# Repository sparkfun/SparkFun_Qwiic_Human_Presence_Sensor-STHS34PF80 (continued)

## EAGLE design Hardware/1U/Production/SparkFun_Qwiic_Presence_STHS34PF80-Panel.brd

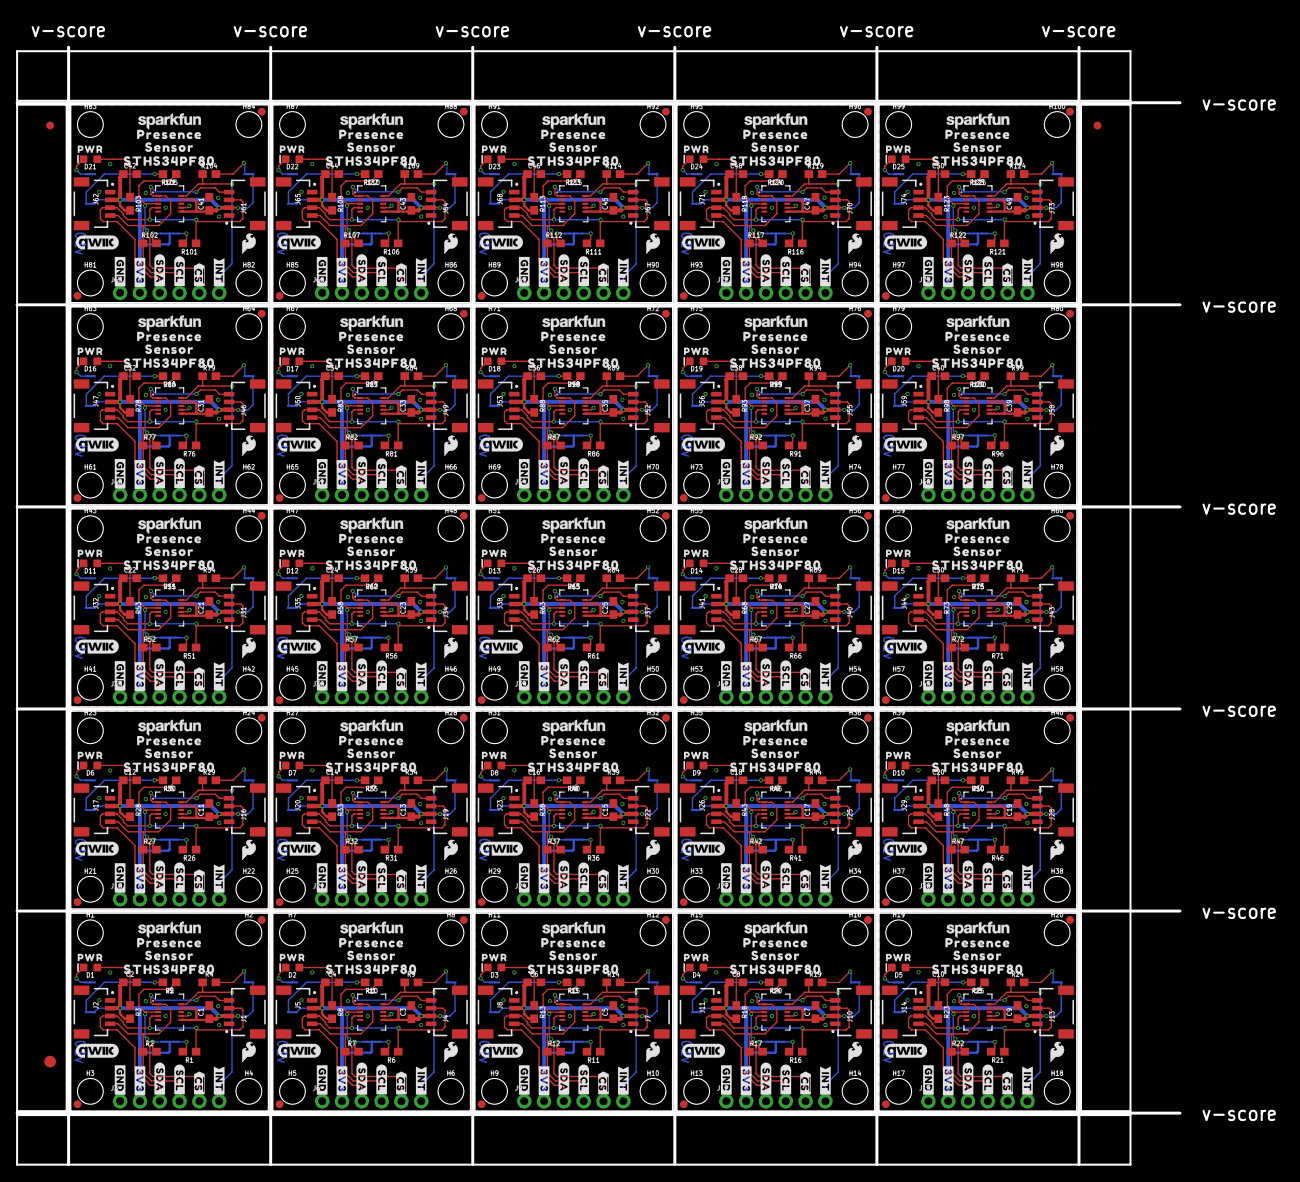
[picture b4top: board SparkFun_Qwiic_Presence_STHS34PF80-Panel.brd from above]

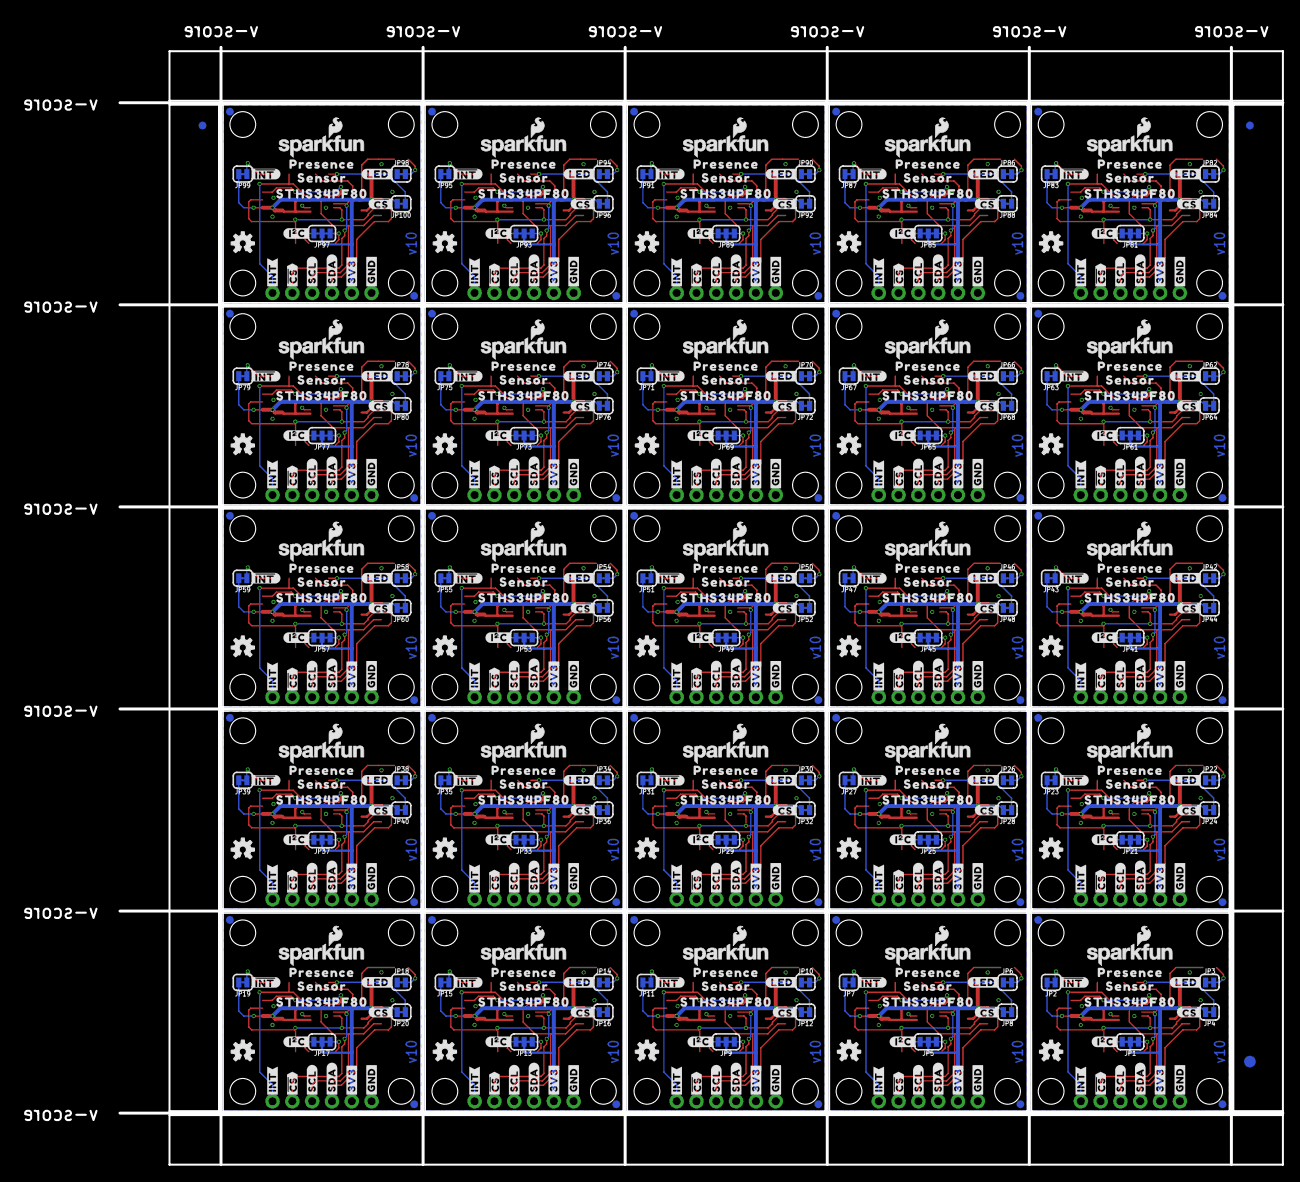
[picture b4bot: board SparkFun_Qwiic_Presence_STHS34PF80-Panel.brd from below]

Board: 2 copper layers, 149.1 x 143.3 mm, 1306 parts (528 on the bottom side), 300 nets.

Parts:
C1, C3, C5, C7, C9, C11, C13, C15, C17, C19, C21, C23, C25, C27, C29, C31, C33, C35, C37, C39, C41, C43, C45, C47, C49: 1.0uF; 0603
C2, C4, C6, C8, C10, C12, C14, C16, C18, C20, C22, C24, C26, C28, C30, C32, C34, C36, C38, C40, C42, C44, C46, C48, C50: 0.1uF; 0603
D1, D2, D3, D4, D5, D6, D7, D8, D9, D10, D11, D12, D13, D14, D15, D16, D17, D18, D19, D20, D21, D22, D23, D24, D25: RED; LED-0603
E$1, E$2, E$3, E$4: FIDUCIAL-1X2
E$5, E$6: FIDUCIAL-1.5X3
FD1, FD2, FD3, FD4, FD5, FD6, FD7, FD8, FD9, FD10, FD11, FD12, FD13, FD14, FD15, FD16, FD17, FD18, FD19, FD20, FD21, FD22, FD23, FD24, FD25, FD26, FD27, FD28, FD29, FD30, FD31, FD32, FD33, FD34, FD35, FD36, FD37, FD38, FD39, FD40, FD41, FD42, FD43, FD44, FD45, FD46, FD47, FD48, FD49, FD50, FD51, FD52, FD53, FD54, FD55, FD56, FD57, FD58, FD59, FD60, FD61, FD62, FD63, FD64, FD65, FD66, FD67, FD68, FD69, FD70, FD71, FD72, FD73, FD74, FD75, FD76, FD77, FD78, FD79, FD80, FD81, FD82, FD83, FD84, FD85, FD86, FD87, FD88, FD89, FD90, FD91, FD92, FD93, FD94, FD95, FD96, FD97, FD98, FD99, FD100: FIDUCIAL1X2; FIDUCIAL-1X2
H1, H2, H3, H4, H5, H6, H7, H8, H9, H10, H11, H12, H13, H14, H15, H16, H17, H18, H19, H20, H21, H22, H23, H24, H25, H26, H27, H28, H29, H30, H31, H32, H33, H34, H35, H36, H37, H38, H39, H40, H41, H42, H43, H44, H45, H46, H47, H48, H49, H50, H51, H52, H53, H54, H55, H56, H57, H58, H59, H60, H61, H62, H63, H64, H65, H66, H67, H68, H69, H70, H71, H72, H73, H74, H75, H76, H77, H78, H79, H80, H81, H82, H83, H84, H85, H86, H87, H88, H89, H90, H91, H92, H93, H94, H95, H96, H97, H98, H99, H100: STAND-OFF
J1, J2, J4, J5, J7, J8, J10, J11, J13, J14, J16, J17, J19, J20, J22, J23, J25, J26, J28, J29, J31, J32, J34, J35, J37, J38, J40, J41, J43, J44, J46, J47, J49, J50, J52, J53, J55, J56, J58, J59, J61, J62, J64, J65, J67, J68, J70, J71, J73, J74: Qwiic; JST04_1MM_RA
J3, J6, J9, J12, J15, J18, J21, J24, J27, J30, J33, J36, J39, J42, J45, J48, J51, J54, J57, J60, J63, J66, J69, J72, J75: 1X06_NO_SILK
JP1, JP5, JP9, JP13, JP17, JP21, JP25, JP29, JP33, JP37, JP41, JP45, JP49, JP53, JP57, JP61, JP65, JP69, JP73, JP77, JP81, JP85, JP89, JP93, JP97: JUMPER-SMT_3_2-NC_TRACE_SILK; SMT-JUMPER_3_2-NC_TRACE_SILK
JP2, JP3, JP4, JP6, JP7, JP8, JP10, JP11, JP12, JP14, JP15, JP16, JP18, JP19, JP20, JP22, JP23, JP24, JP26, JP27, JP28, JP30, JP31, JP32, JP34, JP35, JP36, JP38, JP39, JP40, JP42, JP43, JP44, JP46, JP47, JP48, JP50, JP51, JP52, JP54, JP55, JP56, JP58, JP59, JP60, JP62, JP63, JP64, JP66, JP67, JP68, JP70, JP71, JP72, JP74, JP75, JP76, JP78, JP79, JP80, JP82, JP83, JP84, JP86, JP87, JP88, JP90, JP91, JP92, JP94, JP95, JP96, JP98, JP99, JP100: JUMPER-SMT_2_NC_TRACE_SILK; SMT-JUMPER_2_NC_TRACE_SILK
LOGO1, LOGO5, LOGO11, LOGO16, LOGO21, LOGO26, LOGO31, LOGO36, LOGO41, LOGO46, LOGO51, LOGO56, LOGO61, LOGO66, LOGO71, LOGO76, LOGO81, LOGO86, LOGO91, LOGO96, LOGO101, LOGO106, LOGO111, LOGO116, LOGO121: OSHW-LOGOS; OSHW-LOGO-S
LOGO2, LOGO8, LOGO13, LOGO18, LOGO23, LOGO28, LOGO33, LOGO38, LOGO43, LOGO48, LOGO53, LOGO58, LOGO63, LOGO68, LOGO73, LOGO78, LOGO83, LOGO88, LOGO93, LOGO98, LOGO103, LOGO108, LOGO113, LOGO118, LOGO123: SFE_LOGO_NAME_FLAME.1_INCH; SFE_LOGO_NAME_FLAME_.1
LOGO3, LOGO7, LOGO12, LOGO17, LOGO22, LOGO27, LOGO32, LOGO37, LOGO42, LOGO47, LOGO52, LOGO57, LOGO62, LOGO67, LOGO72, LOGO77, LOGO82, LOGO87, LOGO92, LOGO97, LOGO102, LOGO107, LOGO112, LOGO117, LOGO122: QWIIC_LOGO_CONNECTOR; QWIIC_5.5MM
LOGO4, LOGO10, LOGO15, LOGO20, LOGO25, LOGO30, LOGO35, LOGO40, LOGO45, LOGO50, LOGO55, LOGO60, LOGO65, LOGO70, LOGO75, LOGO80, LOGO85, LOGO90, LOGO95, LOGO100, LOGO105, LOGO110, LOGO115, LOGO120, LOGO125: SFE_LOGO_NAME8_MM; SFE_LOGO_NAME_8MM
LOGO6, LOGO9, LOGO14, LOGO19, LOGO24, LOGO29, LOGO34, LOGO39, LOGO44, LOGO49, LOGO54, LOGO59, LOGO64, LOGO69, LOGO74, LOGO79, LOGO84, LOGO89, LOGO94, LOGO99, LOGO104, LOGO109, LOGO114, LOGO119, LOGO124: SFE_LOGO_FLAME.1_INCH; SFE_LOGO_FLAME_.1
R1, R2, R6, R7, R11, R12, R16, R17, R21, R22, R26, R27, R31, R32, R36, R37, R41, R42, R46, R47, R51, R52, R56, R57, R61, R62, R66, R67, R71, R72, R76, R77, R81, R82, R86, R87, R91, R92, R96, R97, R101, R102, R106, R107, R111, R112, R116, R117, R121, R122: 2.2k; 0603
R3, R8, R13, R18, R23, R28, R33, R38, R43, R48, R53, R58, R63, R68, R73, R78, R83, R88, R93, R98, R103, R108, R113, R118, R123: 1k; 0603
R4, R5, R9, R10, R14, R15, R19, R20, R24, R25, R29, R30, R34, R35, R39, R40, R44, R45, R49, R50, R54, R55, R59, R60, R64, R65, R69, R70, R74, R75, R79, R80, R84, R85, R89, R90, R94, R95, R99, R100, R104, R105, R109, R110, R114, R115, R119, R120, R124, R125: 10k; 0603
U1, U2, U3, U4, U5, U6, U7, U8, U9, U10, U11, U12, U13, U14, U15, U16, U17, U18, U19, U20, U21, U22, U23, U24, U25: STHS34PF80; OLGA-10L
U$1, U$38, U$61, U$84, U$107, U$130, U$153, U$176, U$199, U$222, U$245, U$268, U$291, U$314, U$337, U$360, U$383, U$406, U$429, U$452, U$475, U$498, U$521, U$544, U$567: #I�C#0
U$2, U$30, U$53, U$76, U$99, U$122, U$145, U$168, U$191, U$214, U$237, U$260, U$283, U$306, U$329, U$352, U$375, U$398, U$421, U$444, U$467, U$490, U$513, U$536, U$559: ##CS##0
U$3, U$19, U$29, U$40, U$52, U$63, U$75, U$86, U$98, U$109, U$121, U$132, U$144, U$155, U$167, U$178, U$190, U$201, U$213, U$224, U$236, U$247, U$259, U$270, U$282, U$293, U$305, U$316, U$328, U$339, U$351, U$362, U$374, U$385, U$397, U$408, U$420, U$431, U$443, U$454, U$466, U$477, U$489, U$500, U$512, U$523, U$535, U$546, U$558, U$569: #3V3#0
U$4, U$31, U$54, U$77, U$100, U$123, U$146, U$169, U$192, U$215, U$238, U$261, U$284, U$307, U$330, U$353, U$376, U$399, U$422, U$445, U$468, U$491, U$514, U$537, U$560: #INT#1
U$5, U$6, U$32, U$33, U$55, U$56, U$78, U$79, U$101, U$102, U$124, U$125, U$147, U$148, U$170, U$171, U$193, U$194, U$216, U$217, U$239, U$240, U$262, U$263, U$285, U$286, U$308, U$309, U$331, U$332, U$354, U$355, U$377, U$378, U$400, U$401, U$423, U$424, U$446, U$447, U$469, U$470, U$492, U$493, U$515, U$516, U$538, U$539, U$561, U$562: STHS34PF800
U$7, U$8, U$34, U$35, U$57, U$58, U$80, U$81, U$103, U$104, U$126, U$127, U$149, U$150, U$172, U$173, U$195, U$196, U$218, U$219, U$241, U$242, U$264, U$265, U$287, U$288, U$310, U$311, U$333, U$334, U$356, U$357, U$379, U$380, U$402, U$403, U$425, U$426, U$448, U$449, U$471, U$472, U$494, U$495, U$517, U$518, U$540, U$541, U$563, U$564: PRESENCE0
U$9, U$24, U$47, U$70, U$93, U$116, U$139, U$162, U$185, U$208, U$231, U$254, U$277, U$300, U$323, U$346, U$369, U$392, U$415, U$438, U$461, U$484, U$507, U$530, U$553: PWR11
U$10, U$41, U$64, U$87, U$110, U$133, U$156, U$179, U$202, U$225, U$248, U$271, U$294, U$317, U$340, U$363, U$386, U$409, U$432, U$455, U$478, U$501, U$524, U$547, U$570: ##INT##0
U$11, U$42, U$65, U$88, U$111, U$134, U$157, U$180, U$203, U$226, U$249, U$272, U$295, U$318, U$341, U$364, U$387, U$410, U$433, U$456, U$479, U$502, U$525, U$548, U$571: #SDA#0
U$12, U$14, U$36, U$37, U$59, U$60, U$82, U$83, U$105, U$106, U$128, U$129, U$151, U$152, U$174, U$175, U$197, U$198, U$220, U$221, U$243, U$244, U$266, U$267, U$289, U$290, U$312, U$313, U$335, U$336, U$358, U$359, U$381, U$382, U$404, U$405, U$427, U$428, U$450, U$451, U$473, U$474, U$496, U$497, U$519, U$520, U$542, U$543, U$565, U$566: SENSOR1
U$13, U$43, U$66, U$89, U$112, U$135, U$158, U$181, U$204, U$227, U$250, U$273, U$296, U$319, U$342, U$365, U$388, U$411, U$434, U$457, U$480, U$503, U$526, U$549, U$572: ##CS##1
U$15, U$44, U$67, U$90, U$113, U$136, U$159, U$182, U$205, U$228, U$251, U$274, U$297, U$320, U$343, U$366, U$389, U$412, U$435, U$458, U$481, U$504, U$527, U$550, U$573: #INT#2
U$16, U$18, U$26, U$39, U$49, U$62, U$72, U$85, U$95, U$108, U$118, U$131, U$141, U$154, U$164, U$177, U$187, U$200, U$210, U$223, U$233, U$246, U$256, U$269, U$279, U$292, U$302, U$315, U$325, U$338, U$348, U$361, U$371, U$384, U$394, U$407, U$417, U$430, U$440, U$453, U$463, U$476, U$486, U$499, U$509, U$522, U$532, U$545, U$555, U$568: #GND#4
U$17, U$25, U$48, U$71, U$94, U$117, U$140, U$163, U$186, U$209, U$232, U$255, U$278, U$301, U$324, U$347, U$370, U$393, U$416, U$439, U$462, U$485, U$508, U$531, U$554: #LED#10
U$20, U$27, U$50, U$73, U$96, U$119, U$142, U$165, U$188, U$211, U$234, U$257, U$280, U$303, U$326, U$349, U$372, U$395, U$418, U$441, U$464, U$487, U$510, U$533, U$556: #SDA#5
U$21, U$28, U$51, U$74, U$97, U$120, U$143, U$166, U$189, U$212, U$235, U$258, U$281, U$304, U$327, U$350, U$373, U$396, U$419, U$442, U$465, U$488, U$511, U$534, U$557: #SCL#6
U$22, U$45, U$68, U$91, U$114, U$137, U$160, U$183, U$206, U$229, U$252, U$275, U$298, U$321, U$344, U$367, U$390, U$413, U$436, U$459, U$482, U$505, U$528, U$551, U$574: #SCL#0
U$23, U$46, U$69, U$92, U$115, U$138, U$161, U$184, U$207, U$230, U$253, U$276, U$299, U$322, U$345, U$368, U$391, U$414, U$437, U$460, U$483, U$506, U$529, U$552, U$575: ##CS#0

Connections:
3.3V: C1.1, C2.1, J1.2, J2.2, J3.2, JP1.2, JP2.2, JP4.2, R3.2, U2.6, U2.9
3.3V1: C3.1, C4.1, J4.2, J5.2, J6.2, JP5.2, JP7.2, JP8.2, R8.2, U1.6, U1.9
3.3V2: C5.1, C6.1, J7.2, J8.2, J9.2, JP9.2, JP11.2, JP12.2, R13.2, U3.6, U3.9
3.3V3: C7.1, C8.1, J10.2, J11.2, J12.2, JP13.2, JP15.2, JP16.2, R18.2, U4.6, U4.9
3.3V4: C9.1, C10.1, J13.2, J14.2, J15.2, JP17.2, JP19.2, JP20.2, R23.2, U5.6, U5.9
3.3V5: C11.1, C12.1, J16.2, J17.2, J18.2, JP21.2, JP23.2, JP24.2, R28.2, U6.6, U6.9
3.3V6: C13.1, C14.1, J19.2, J20.2, J21.2, JP25.2, JP27.2, JP28.2, R33.2, U7.6, U7.9
3.3V7: C15.1, C16.1, J22.2, J23.2, J24.2, JP29.2, JP31.2, JP32.2, R38.2, U8.6, U8.9
3.3V8: C17.1, C18.1, J25.2, J26.2, J27.2, JP33.2, JP35.2, JP36.2, R43.2, U9.6, U9.9
3.3V9: C19.1, C20.1, J28.2, J29.2, J30.2, JP37.2, JP39.2, JP40.2, R48.2, U10.6, U10.9
3.3V10: C21.1, C22.1, J31.2, J32.2, J33.2, JP41.2, JP43.2, JP44.2, R53.2, U11.6, U11.9
3.3V11: C23.1, C24.1, J34.2, J35.2, J36.2, JP45.2, JP47.2, JP48.2, R58.2, U12.6, U12.9
3.3V12: C25.1, C26.1, J37.2, J38.2, J39.2, JP49.2, JP51.2, JP52.2, R63.2, U13.6, U13.9
3.3V13: C27.1, C28.1, J40.2, J41.2, J42.2, JP53.2, JP55.2, JP56.2, R68.2, U14.6, U14.9
3.3V14: C29.1, C30.1, J43.2, J44.2, J45.2, JP57.2, JP59.2, JP60.2, R73.2, U15.6, U15.9
3.3V15: C31.1, C32.1, J46.2, J47.2, J48.2, JP61.2, JP63.2, JP64.2, R78.2, U16.6, U16.9
3.3V16: C33.1, C34.1, J49.2, J50.2, J51.2, JP65.2, JP67.2, JP68.2, R83.2, U17.6, U17.9
3.3V17: C35.1, C36.1, J52.2, J53.2, J54.2, JP69.2, JP71.2, JP72.2, R88.2, U18.6, U18.9
3.3V18: C37.1, C38.1, J55.2, J56.2, J57.2, JP73.2, JP75.2, JP76.2, R93.2, U19.6, U19.9
3.3V19: C39.1, C40.1, J58.2, J59.2, J60.2, JP77.2, JP79.2, JP80.2, R98.2, U20.6, U20.9
3.3V20: C41.1, C42.1, J61.2, J62.2, J63.2, JP81.2, JP83.2, JP84.2, R103.2, U21.6, U21.9
3.3V21: C43.1, C44.1, J64.2, J65.2, J66.2, JP85.2, JP87.2, JP88.2, R108.2, U22.6, U22.9
3.3V22: C45.1, C46.1, J67.2, J68.2, J69.2, JP89.2, JP91.2, JP92.2, R113.2, U23.6, U23.9
3.3V23: C47.1, C48.1, J70.2, J71.2, J72.2, JP93.2, JP95.2, JP96.2, R118.2, U24.6, U24.9
3.3V24: C49.1, C50.1, J73.2, J74.2, J75.2, JP97.2, JP99.2, JP100.2, R123.2, U25.6, U25.9
!CS!: J3.5, R5.1, U2.3
!CS!1: J6.5, R10.1, U1.3
!CS!2: J9.5, R15.1, U3.3
!CS!3: J12.5, R20.1, U4.3
!CS!4: J15.5, R25.1, U5.3
!CS!5: J18.5, R30.1, U6.3
!CS!6: J21.5, R35.1, U7.3
!CS!7: J24.5, R40.1, U8.3
!CS!8: J27.5, R45.1, U9.3
!CS!9: J30.5, R50.1, U10.3
!CS!10: J33.5, R55.1, U11.3
!CS!11: J36.5, R60.1, U12.3
!CS!12: J39.5, R65.1, U13.3
!CS!13: J42.5, R70.1, U14.3
!CS!14: J45.5, R75.1, U15.3
!CS!15: J48.5, R80.1, U16.3
!CS!16: J51.5, R85.1, U17.3
!CS!17: J54.5, R90.1, U18.3
!CS!18: J57.5, R95.1, U19.3
!CS!19: J60.5, R100.1, U20.3
!CS!20: J63.5, R105.1, U21.3
!CS!21: J66.5, R110.1, U22.3
!CS!22: J69.5, R115.1, U23.3
!CS!23: J72.5, R120.1, U24.3
!CS!24: J75.5, R125.1, U25.3
GND: C1.2, C2.2, J1.1, J2.1, J3.1, JP3.1, U2.2, U2.7, U2.8
GND1: C3.2, C4.2, J4.1, J5.1, J6.1, JP6.1, U1.2, U1.7, U1.8
GND2: C5.2, C6.2, J7.1, J8.1, J9.1, JP10.1, U3.2, U3.7, U3.8
GND3: C7.2, C8.2, J10.1, J11.1, J12.1, JP14.1, U4.2, U4.7, U4.8
GND4: C9.2, C10.2, J13.1, J14.1, J15.1, JP18.1, U5.2, U5.7, U5.8
GND5: C11.2, C12.2, J16.1, J17.1, J18.1, JP22.1, U6.2, U6.7, U6.8
GND6: C13.2, C14.2, J19.1, J20.1, J21.1, JP26.1, U7.2, U7.7, U7.8
GND7: C15.2, C16.2, J22.1, J23.1, J24.1, JP30.1, U8.2, U8.7, U8.8
GND8: C17.2, C18.2, J25.1, J26.1, J27.1, JP34.1, U9.2, U9.7, U9.8
GND9: C19.2, C20.2, J28.1, J29.1, J30.1, JP38.1, U10.2, U10.7, U10.8
GND10: C21.2, C22.2, J31.1, J32.1, J33.1, JP42.1, U11.2, U11.7, U11.8
GND11: C23.2, C24.2, J34.1, J35.1, J36.1, JP46.1, U12.2, U12.7, U12.8
GND12: C25.2, C26.2, J37.1, J38.1, J39.1, JP50.1, U13.2, U13.7, U13.8
GND13: C27.2, C28.2, J40.1, J41.1, J42.1, JP54.1, U14.2, U14.7, U14.8
GND14: C29.2, C30.2, J43.1, J44.1, J45.1, JP58.1, U15.2, U15.7, U15.8
GND15: C31.2, C32.2, J46.1, J47.1, J48.1, JP62.1, U16.2, U16.7, U16.8
GND16: C33.2, C34.2, J49.1, J50.1, J51.1, JP66.1, U17.2, U17.7, U17.8
GND17: C35.2, C36.2, J52.1, J53.1, J54.1, JP70.1, U18.2, U18.7, U18.8
GND18: C37.2, C38.2, J55.1, J56.1, J57.1, JP74.1, U19.2, U19.7, U19.8
GND19: C39.2, C40.2, J58.1, J59.1, J60.1, JP78.1, U20.2, U20.7, U20.8
GND20: C41.2, C42.2, J61.1, J62.1, J63.1, JP82.1, U21.2, U21.7, U21.8
GND21: C43.2, C44.2, J64.1, J65.1, J66.1, JP86.1, U22.2, U22.7, U22.8
GND22: C45.2, C46.2, J67.1, J68.1, J69.1, JP90.1, U23.2, U23.7, U23.8
GND23: C47.2, C48.2, J70.1, J71.1, J72.1, JP94.1, U24.2, U24.7, U24.8
GND24: C49.2, C50.2, J73.1, J74.1, J75.1, JP98.1, U25.2, U25.7, U25.8
INT: J3.6, R4.1, U2.10
INT1: J6.6, R9.1, U1.10
INT2: J9.6, R14.1, U3.10
INT3: J12.6, R19.1, U4.10
INT4: J15.6, R24.1, U5.10
INT5: J18.6, R29.1, U6.10
INT6: J21.6, R34.1, U7.10
INT7: J24.6, R39.1, U8.10
INT8: J27.6, R44.1, U9.10
INT9: J30.6, R49.1, U10.10
INT10: J33.6, R54.1, U11.10
INT11: J36.6, R59.1, U12.10
INT12: J39.6, R64.1, U13.10
INT13: J42.6, R69.1, U14.10
INT14: J45.6, R74.1, U15.10
INT15: J48.6, R79.1, U16.10
INT16: J51.6, R84.1, U17.10
INT17: J54.6, R89.1, U18.10
INT18: J57.6, R94.1, U19.10
INT19: J60.6, R99.1, U20.10
INT20: J63.6, R104.1, U21.10
INT21: J66.6, R109.1, U22.10
INT22: J69.6, R114.1, U23.10
INT23: J72.6, R119.1, U24.10
INT24: J75.6, R124.1, U25.10
unnamed: D1.C, JP3.2
unnamed: JP1.3, R1.2
unnamed: JP1.1, R2.2
unnamed: D1.A, R3.1
unnamed: JP2.1, R4.2
unnamed: JP4.1, R5.2
unnamed: JP5.3, R6.2
unnamed: JP5.1, R7.2
unnamed: D2.A, R8.1
unnamed: JP7.1, R9.2
unnamed: D2.C, JP6.2
unnamed: JP8.1, R10.2
unnamed: JP9.3, R11.2
unnamed: JP9.1, R12.2
unnamed: D3.A, R13.1
unnamed: JP11.1, R14.2
unnamed: D3.C, JP10.2
unnamed: JP12.1, R15.2
unnamed: JP13.3, R16.2
unnamed: JP13.1, R17.2
unnamed: D4.A, R18.1
unnamed: JP15.1, R19.2
unnamed: D4.C, JP14.2
unnamed: JP16.1, R20.2
unnamed: JP17.3, R21.2
unnamed: JP17.1, R22.2
unnamed: D5.A, R23.1
unnamed: JP19.1, R24.2
unnamed: D5.C, JP18.2
unnamed: JP20.1, R25.2
unnamed: JP21.3, R26.2
unnamed: JP21.1, R27.2
unnamed: D6.A, R28.1
unnamed: JP23.1, R29.2
unnamed: D6.C, JP22.2
unnamed: JP24.1, R30.2
unnamed: JP25.3, R31.2
unnamed: JP25.1, R32.2
unnamed: D7.A, R33.1
unnamed: JP27.1, R34.2
unnamed: D7.C, JP26.2
unnamed: JP28.1, R35.2
unnamed: JP29.3, R36.2
unnamed: JP29.1, R37.2
unnamed: D8.A, R38.1
unnamed: JP31.1, R39.2
unnamed: D8.C, JP30.2
unnamed: JP32.1, R40.2
unnamed: JP33.3, R41.2
unnamed: JP33.1, R42.2
unnamed: D9.A, R43.1
unnamed: JP35.1, R44.2
unnamed: D9.C, JP34.2
unnamed: JP36.1, R45.2
unnamed: JP37.3, R46.2
unnamed: JP37.1, R47.2
unnamed: D10.A, R48.1
unnamed: JP39.1, R49.2
unnamed: D10.C, JP38.2
unnamed: JP40.1, R50.2
unnamed: JP41.3, R51.2
unnamed: JP41.1, R52.2
unnamed: D11.A, R53.1
unnamed: JP43.1, R54.2
unnamed: D11.C, JP42.2
unnamed: JP44.1, R55.2
unnamed: JP45.3, R56.2
unnamed: JP45.1, R57.2
unnamed: D12.A, R58.1
unnamed: JP47.1, R59.2
unnamed: D12.C, JP46.2
unnamed: JP48.1, R60.2
unnamed: JP49.3, R61.2
unnamed: JP49.1, R62.2
unnamed: D13.A, R63.1
unnamed: JP51.1, R64.2
unnamed: D13.C, JP50.2
unnamed: JP52.1, R65.2
unnamed: JP53.3, R66.2
unnamed: JP53.1, R67.2
unnamed: D14.A, R68.1
unnamed: JP55.1, R69.2
unnamed: D14.C, JP54.2
unnamed: JP56.1, R70.2
unnamed: JP57.3, R71.2
unnamed: JP57.1, R72.2
unnamed: D15.A, R73.1
unnamed: JP59.1, R74.2
unnamed: D15.C, JP58.2
unnamed: JP60.1, R75.2
unnamed: JP61.3, R76.2
unnamed: JP61.1, R77.2
unnamed: D16.A, R78.1
unnamed: JP63.1, R79.2
unnamed: D16.C, JP62.2
unnamed: JP64.1, R80.2
unnamed: JP65.3, R81.2
unnamed: JP65.1, R82.2
unnamed: D17.A, R83.1
unnamed: JP67.1, R84.2
unnamed: D17.C, JP66.2
unnamed: JP68.1, R85.2
unnamed: JP69.3, R86.2
unnamed: JP69.1, R87.2
unnamed: D18.A, R88.1
unnamed: JP71.1, R89.2
unnamed: D18.C, JP70.2
unnamed: JP72.1, R90.2
unnamed: JP73.3, R91.2
unnamed: JP73.1, R92.2
unnamed: D19.A, R93.1
unnamed: JP75.1, R94.2
unnamed: D19.C, JP74.2
unnamed: JP76.1, R95.2
unnamed: JP77.3, R96.2
unnamed: JP77.1, R97.2
unnamed: D20.A, R98.1
unnamed: JP79.1, R99.2
unnamed: D20.C, JP78.2
unnamed: JP80.1, R100.2
unnamed: JP81.3, R101.2
unnamed: JP81.1, R102.2
unnamed: D21.A, R103.1
unnamed: JP83.1, R104.2
unnamed: D21.C, JP82.2
unnamed: JP84.1, R105.2
unnamed: JP85.3, R106.2
unnamed: JP85.1, R107.2
unnamed: D22.A, R108.1
unnamed: JP87.1, R109.2
unnamed: D22.C, JP86.2
unnamed: JP88.1, R110.2
unnamed: JP89.3, R111.2
unnamed: JP89.1, R112.2
unnamed: D23.A, R113.1
unnamed: JP91.1, R114.2
unnamed: D23.C, JP90.2
unnamed: JP92.1, R115.2
unnamed: JP93.3, R116.2
unnamed: JP93.1, R117.2
unnamed: D24.A, R118.1
unnamed: JP95.1, R119.2
unnamed: D24.C, JP94.2
unnamed: JP96.1, R120.2
unnamed: JP97.3, R121.2
unnamed: JP97.1, R122.2
unnamed: D25.A, R123.1
unnamed: JP99.1, R124.2
unnamed: D25.C, JP98.2
unnamed: JP100.1, R125.2
SCL: J1.4, J2.4, J3.4, R2.1, U2.1
SCL1: J4.4, J5.4, J6.4, R7.1, U1.1
SCL2: J7.4, J8.4, J9.4, R12.1, U3.1
SCL3: J10.4, J11.4, J12.4, R17.1, U4.1
SCL4: J13.4, J14.4, J15.4, R22.1, U5.1
SCL5: J16.4, J17.4, J18.4, R27.1, U6.1
SCL6: J19.4, J20.4, J21.4, R32.1, U7.1
SCL7: J22.4, J23.4, J24.4, R37.1, U8.1
SCL8: J25.4, J26.4, J27.4, R42.1, U9.1
SCL9: J28.4, J29.4, J30.4, R47.1, U10.1
SCL10: J31.4, J32.4, J33.4, R52.1, U11.1
SCL11: J34.4, J35.4, J36.4, R57.1, U12.1
SCL12: J37.4, J38.4, J39.4, R62.1, U13.1
SCL13: J40.4, J41.4, J42.4, R67.1, U14.1
SCL14: J43.4, J44.4, J45.4, R72.1, U15.1
SCL15: J46.4, J47.4, J48.4, R77.1, U16.1
SCL16: J49.4, J50.4, J51.4, R82.1, U17.1
SCL17: J52.4, J53.4, J54.4, R87.1, U18.1
SCL18: J55.4, J56.4, J57.4, R92.1, U19.1
SCL19: J58.4, J59.4, J60.4, R97.1, U20.1
SCL20: J61.4, J62.4, J63.4, R102.1, U21.1
SCL21: J64.4, J65.4, J66.4, R107.1, U22.1
SCL22: J67.4, J68.4, J69.4, R112.1, U23.1
SCL23: J70.4, J71.4, J72.4, R117.1, U24.1
SCL24: J73.4, J74.4, J75.4, R122.1, U25.1
SDA: J1.3, J2.3, J3.3, R1.1, U2.4
SDA1: J4.3, J5.3, J6.3, R6.1, U1.4
SDA2: J7.3, J8.3, J9.3, R11.1, U3.4
SDA3: J10.3, J11.3, J12.3, R16.1, U4.4
SDA4: J13.3, J14.3, J15.3, R21.1, U5.4
SDA5: J16.3, J17.3, J18.3, R26.1, U6.4
SDA6: J19.3, J20.3, J21.3, R31.1, U7.4
SDA7: J22.3, J23.3, J24.3, R36.1, U8.4
SDA8: J25.3, J26.3, J27.3, R41.1, U9.4
SDA9: J28.3, J29.3, J30.3, R46.1, U10.4
SDA10: J31.3, J32.3, J33.3, R51.1, U11.4
SDA11: J34.3, J35.3, J36.3, R56.1, U12.4
SDA12: J37.3, J38.3, J39.3, R61.1, U13.4
SDA13: J40.3, J41.3, J42.3, R66.1, U14.4
SDA14: J43.3, J44.3, J45.3, R71.1, U15.4
SDA15: J46.3, J47.3, J48.3, R76.1, U16.4
SDA16: J49.3, J50.3, J51.3, R81.1, U17.4
SDA17: J52.3, J53.3, J54.3, R86.1, U18.4
SDA18: J55.3, J56.3, J57.3, R91.1, U19.4
SDA19: J58.3, J59.3, J60.3, R96.1, U20.4
SDA20: J61.3, J62.3, J63.3, R101.1, U21.4
SDA21: J64.3, J65.3, J66.3, R106.1, U22.4
SDA22: J67.3, J68.3, J69.3, R111.1, U23.4
SDA23: J70.3, J71.3, J72.3, R116.1, U24.4
SDA24: J73.3, J74.3, J75.3, R121.1, U25.4
